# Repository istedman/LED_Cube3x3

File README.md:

# LED_Cube3x3
Arduino derived LED cube, simple 3x3 array based on ideas from Instructables, https://www.instructables.com/LED-Cube-and-Arduino-Lib/

There is a video of it running here:
https://youtu.be/xb_SiZRE9oY

My customised software is in the ledcube folder with the Arduino source file.

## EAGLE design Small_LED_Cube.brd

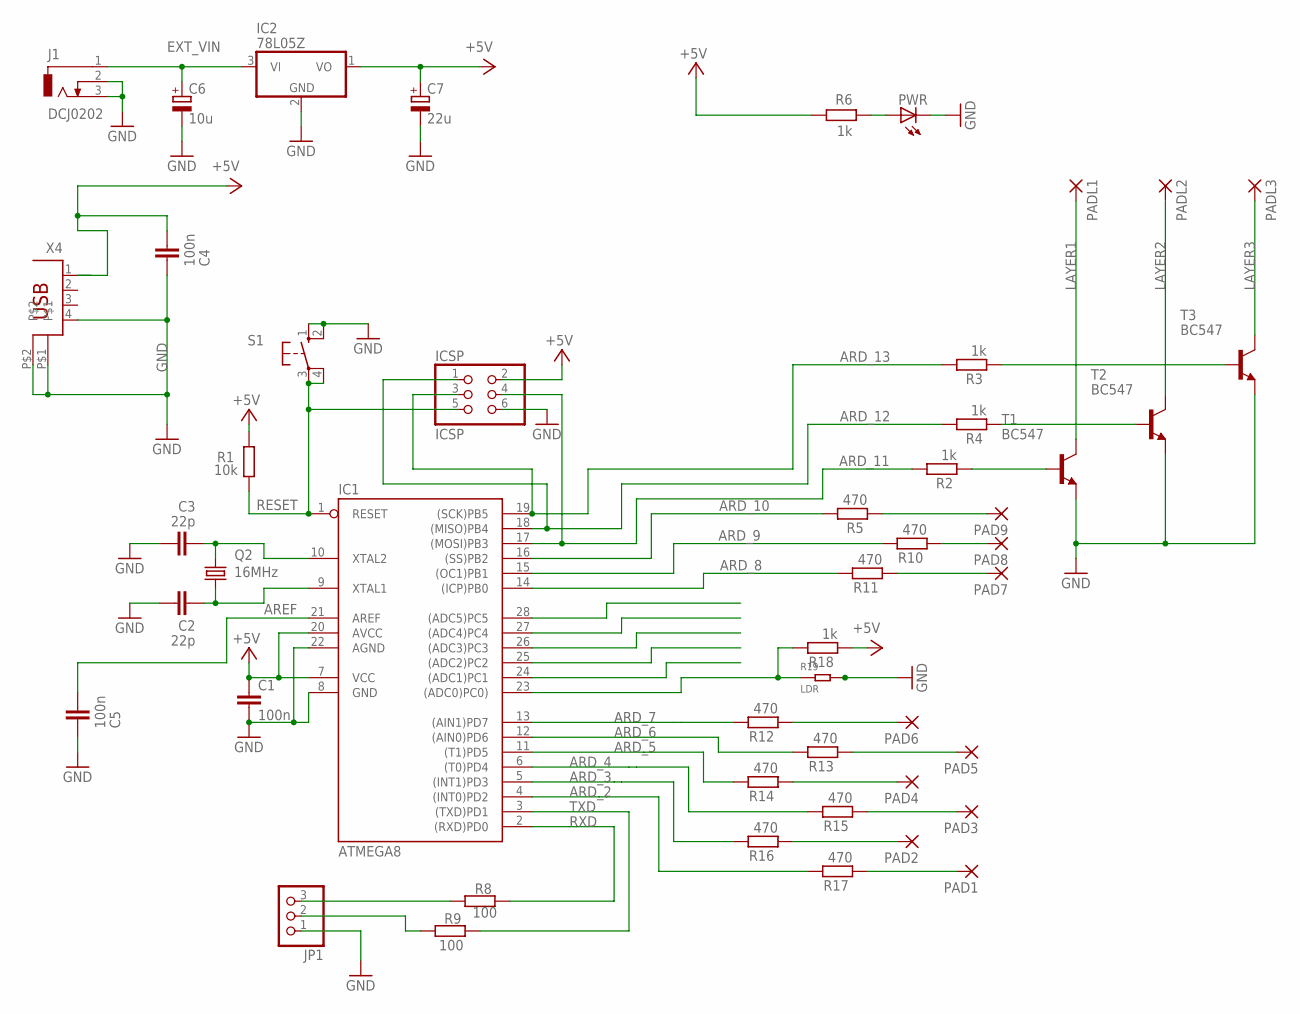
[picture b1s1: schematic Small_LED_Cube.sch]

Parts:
C1, C4, C5: 100n; C050-025X075
C2, C3: 22p; C025-024X044
C6: 10u; E2,5-5
C7: 22u; E2,5-5
IC1: ATMEGA8; DIL28-3
IC2: 78L05Z; TO92
ICSP: ICSP; 2X03
J1: DCJ0202
JP1: PINHD-1X3; 1X03
PAD1, PAD2, PAD3, PAD4, PAD5, PAD6, PAD7, PAD8, PAD9: 1,6/0,9
PADL1, PADL2, PADL3: 1,6/0,9
PWR: LED3MM
Q2: 16MHz; HC49/S
R1: 10k; 0204/7@1
R2, R3, R4, R6, R18: 1k; 0204/7@1
R5, R10, R11, R12, R13, R14, R15, R16, R17: 470; 0204/7@1
R8, R9: 100; 0204/7@1
R19: LDR; PR-2.8-4.2X4.9MM
S1: 10-XX; B3F-10XX
T1, T2, T3: BC547; TO92
X4: PN61729

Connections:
+5V: C1.1, C4.1, C7.+, IC1.7 (VCC), IC1.20 (AVCC), IC2.1 (VO), ICSP.2, R1.2, R6.1, R18.2, X4.1
ARD_2: IC1.4 ((INT0)PD2), R17.1
ARD_3: IC1.5 ((INT1)PD3), R16.1
ARD_4: IC1.6 ((T0)PD4), R15.1
ARD_5: IC1.11 ((T1)PD5), R14.1
ARD_6: IC1.12 ((AIN0)PD6), R13.1
ARD_7: IC1.13 ((AIN1)PD7), R12.1
ARD_8: IC1.14 ((ICP)PB0), R11.1
ARD_9: IC1.15 ((OC1)PB1), R10.1
ARD_10: IC1.16 ((SS)PB2), R5.1
ARD_11: IC1.17 ((MOSI)PB3), ICSP.4, R2.1
ARD_12: IC1.18 ((MISO)PB4), ICSP.1, R4.1
ARD_13: IC1.19 ((SCK)PB5), ICSP.3, R3.1
AREF: C5.1, IC1.21 (AREF)
EXT_VIN: C6.+, IC2.3 (VI), J1.1
GND: C1.2, C2.1, C3.1, C4.2, C5.2, C6.-, C7.-, IC1.8 (GND), IC1.22 (AGND), IC2.2 (GND), ICSP.6, J1.2, J1.3, JP1.1, PWR.K (C), R19.2, S1.1 (S), S1.2 (S1), T1.1 (E), T2.1 (E), T3.1 (E), X4.4, X4.P$1, X4.P$2
LAYER1: PADL1.1, T1.3 (C)
LAYER2: PADL2.1, T2.3 (C)
LAYER3: PADL3.1, T3.3 (C)
unnamed: PWR.A, R6.2
unnamed: PAD9.1, R5.2
unnamed: C2.2, IC1.9 (XTAL1), Q2.1
unnamed: C3.2, IC1.10 (XTAL2), Q2.2
unnamed: JP1.3, R8.2
unnamed: PAD6.1, R12.2
unnamed: PAD5.1, R13.2
unnamed: PAD4.1, R14.2
unnamed: IC1.23 ((ADC0)PC0)), R18.1, R19.1
unnamed: PAD3.1, R15.2
unnamed: JP1.2, R9.2
unnamed: R4.2, T2.2 (B)
unnamed: R2.2, T1.2 (B)
unnamed: R3.2, T3.2 (B)
unnamed: PAD2.1, R16.2
unnamed: PAD1.1, R17.2
unnamed: PAD7.1, R11.2
unnamed: PAD8.1, R10.2
RESET: IC1.1 (RESET), ICSP.5, R1.1, S1.3, S1.4 (P1)
RXD: IC1.2 ((RXD)PD0), R8.1
TXD: IC1.3 ((TXD)PD1), R9.1

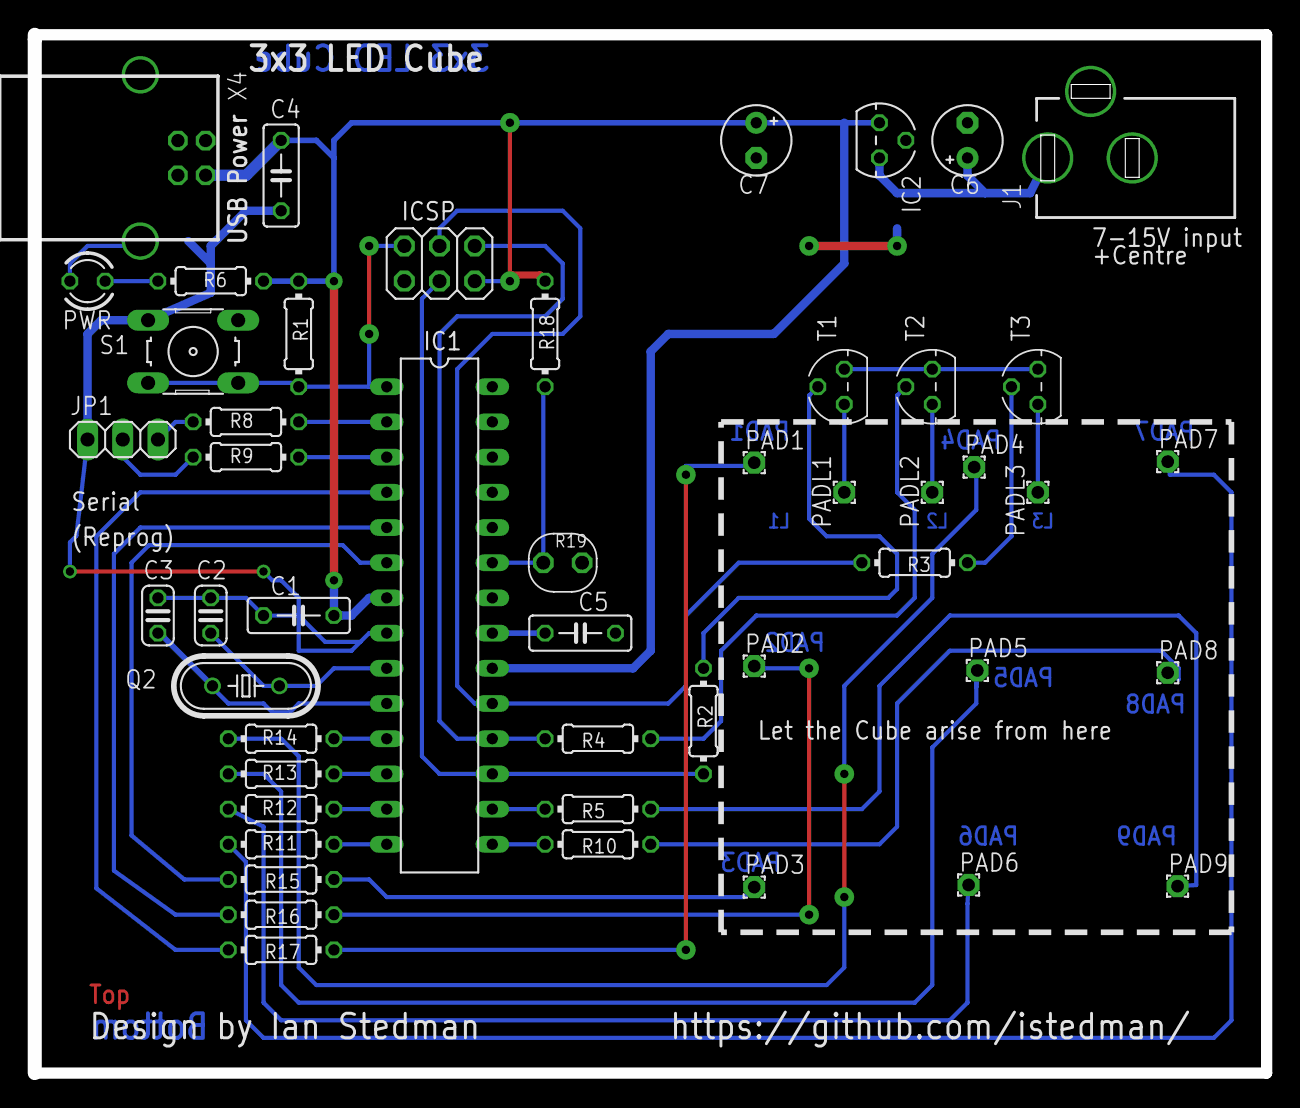
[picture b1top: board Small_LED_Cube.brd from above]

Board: 2 copper layers, 88.9 x 74.9 mm, 49 parts (0 on the bottom side), 40 nets.

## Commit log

2018-03-01 Native Eagle 7.7 CAD files, Schematic and PCB
2018-03-01 Schematic and PCB overlay
2021-09-13 Add files via upload
    My modified example code from the original article here, https://www.instructables.com/LED-Cube-and-Arduino-Lib/
    It has a nice raindrop pattern, not shown in the video.
